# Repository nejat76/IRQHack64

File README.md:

# IRQHack64
Software &amp; Hardware stuff for IRQHack64

Firmware stuff for IRQHack64 will be here. 

- *IRQHack64V2* : This is the V2 firmware yet in alpha stage.
- *IRQHack64* : Existing firmware will be here once it's been cleaned and gets ready for publishing

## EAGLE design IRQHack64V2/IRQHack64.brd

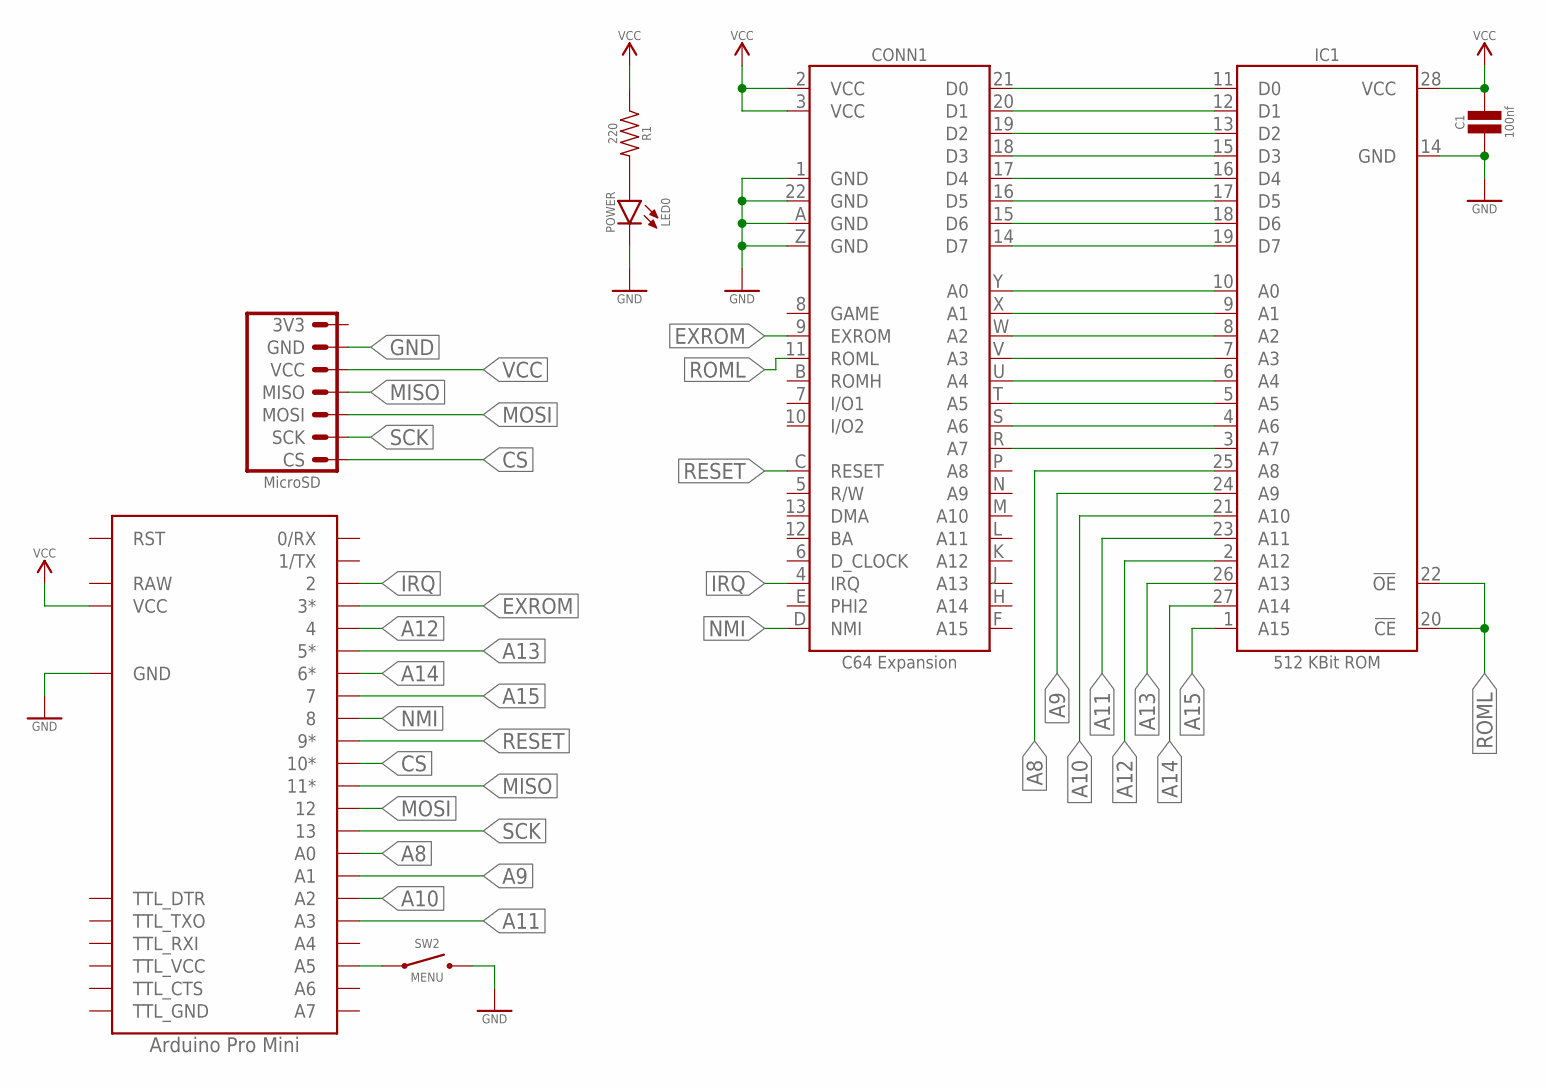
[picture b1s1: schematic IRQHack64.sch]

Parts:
C1: 100nf; CAPACITOR_CERAMIC_0.2
CONN1: C64 Expansion; C64_CARTRIDGE
IC1: 512 KBit ROM; DIP28W
IC2: Arduino Pro Mini; PROMINI
LED0: POWER; LED_03MM
R1: 220; RESISTOR_0.3
SD1: MicroSD; MICROSD_RTL
SW2: MENU; SWITCH_THT_SIDEWITHPADS

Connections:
A0: CONN1.Y (A0), IC1.10 (A0)
A1: CONN1.X (A1), IC1.9 (A1)
A2: CONN1.W (A2), IC1.8 (A2)
A3: CONN1.V (A3), IC1.7 (A3)
A4: CONN1.U (A4), IC1.6 (A4)
A5: CONN1.T (A5), IC1.5 (A5)
A6: CONN1.S (A6), IC1.4 (A6)
A7: CONN1.R (A7), IC1.3 (A7)
A8: IC1.25 (A8), IC2.A0
A9: IC1.24 (A9), IC2.A1
A10: IC1.21 (A10), IC2.A2
A11: IC1.23 (A11), IC2.A3
A12: IC1.2 (A12), IC2.4
A13: IC1.26 (A13), IC2.5*
A14: IC1.27 (A14), IC2.6*
A15: IC1.1 (A15), IC2.7
CS: IC2.10*, SD1.CS
D0: CONN1.21 (D0), IC1.11 (D0)
D1: CONN1.20 (D1), IC1.12 (D1)
D2: CONN1.19 (D2), IC1.13 (D2)
D3: CONN1.18 (D3), IC1.15 (D3)
D4: CONN1.17 (D4), IC1.16 (D4)
D5: CONN1.16 (D5), IC1.17 (D5)
D6: CONN1.15 (D6), IC1.18 (D6)
D7: CONN1.14 (D7), IC1.19 (D7)
EXROM: CONN1.9 (EXROM), IC2.3*
GND: C1.1, CONN1.1 (GND), CONN1.22 (GND), CONN1.A (GND), CONN1.Z (GND), IC1.14 (GND), IC2.GND@1 (GND), IC2.GND@2 (GND), LED0.CATHODE (C), SD1.GND, SW2.2, SW2.BOTTOM (2)
IRQ: CONN1.4 (IRQ), IC2.2
LED0_1: LED0.ANODE (A), R1.2
MISO: IC2.11*, SD1.MISO
MOSI: IC2.12, SD1.MOSI
unnamed: IC2.A5@1 (A5), IC2.A5@2 (A5), SW2.1, SW2.TOP (1)
NMI: CONN1.D (NMI), IC2.8
RESET: CONN1.C (RESET), IC2.9*
ROML: CONN1.11 (ROML), IC1.20 (!CE), IC1.22 (!OE)
SCK: IC2.13, SD1.SCK
VCC: C1.2, CONN1.2 (VCC), CONN1.3 (VCC), IC1.28 (VCC), IC2.VCC, R1.1, SD1.VCC

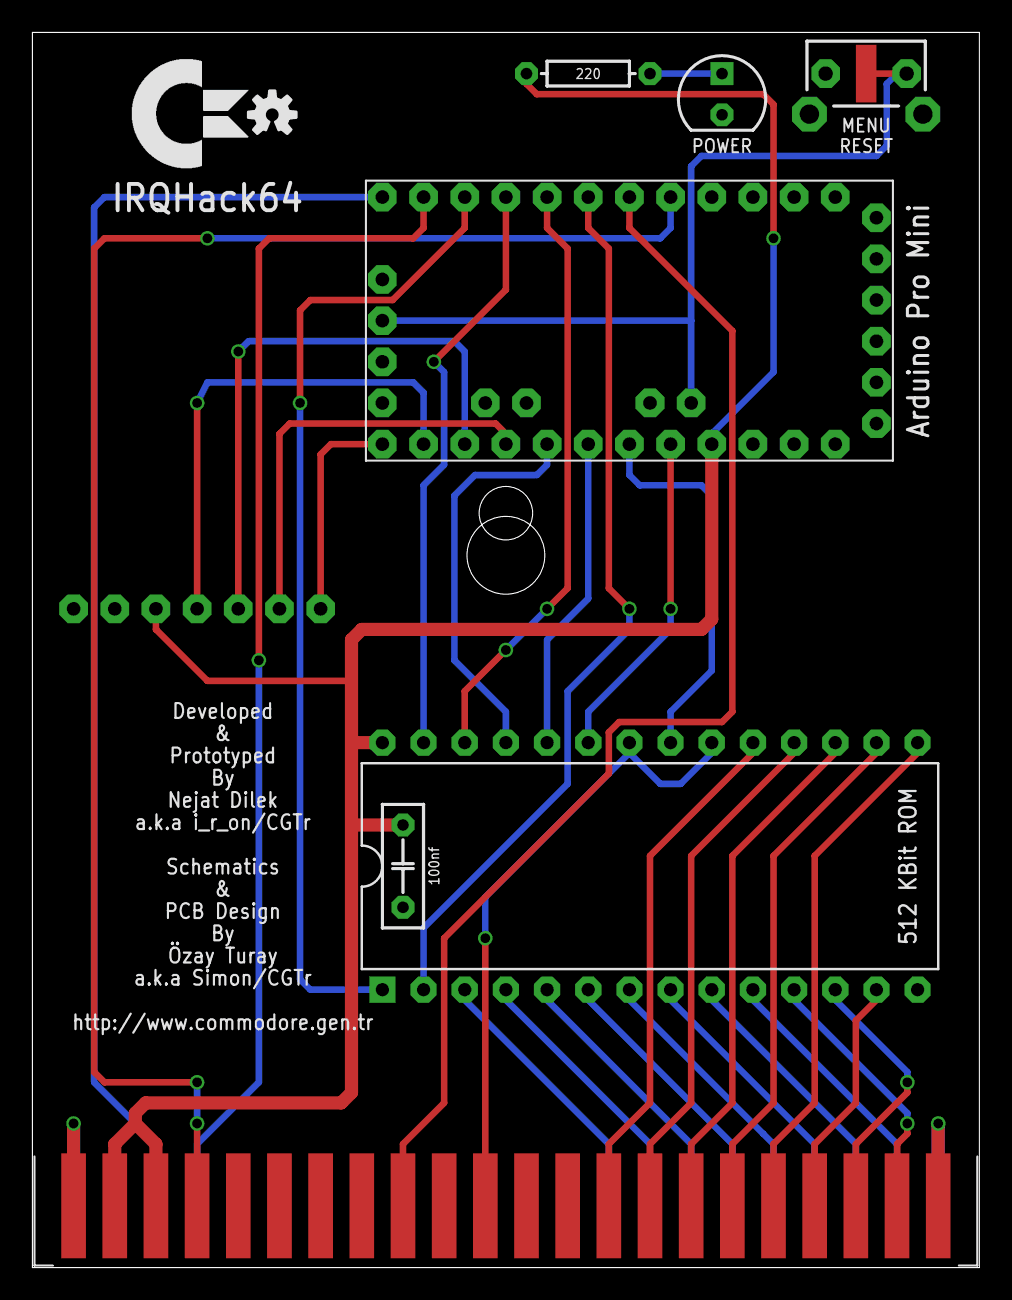
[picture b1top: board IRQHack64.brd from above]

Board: 2 copper layers, 58.4 x 76.2 mm, 9 parts (1 on the bottom side), 37 nets.

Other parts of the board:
LOGO1: OSHW_LOGO_SMALL

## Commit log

2019-06-20 IRQHack64V2
2019-06-20 Added license
2019-06-20 Documentation change
2019-06-20 Removed readme.txt
2019-06-20 Removed Runtime.txt
